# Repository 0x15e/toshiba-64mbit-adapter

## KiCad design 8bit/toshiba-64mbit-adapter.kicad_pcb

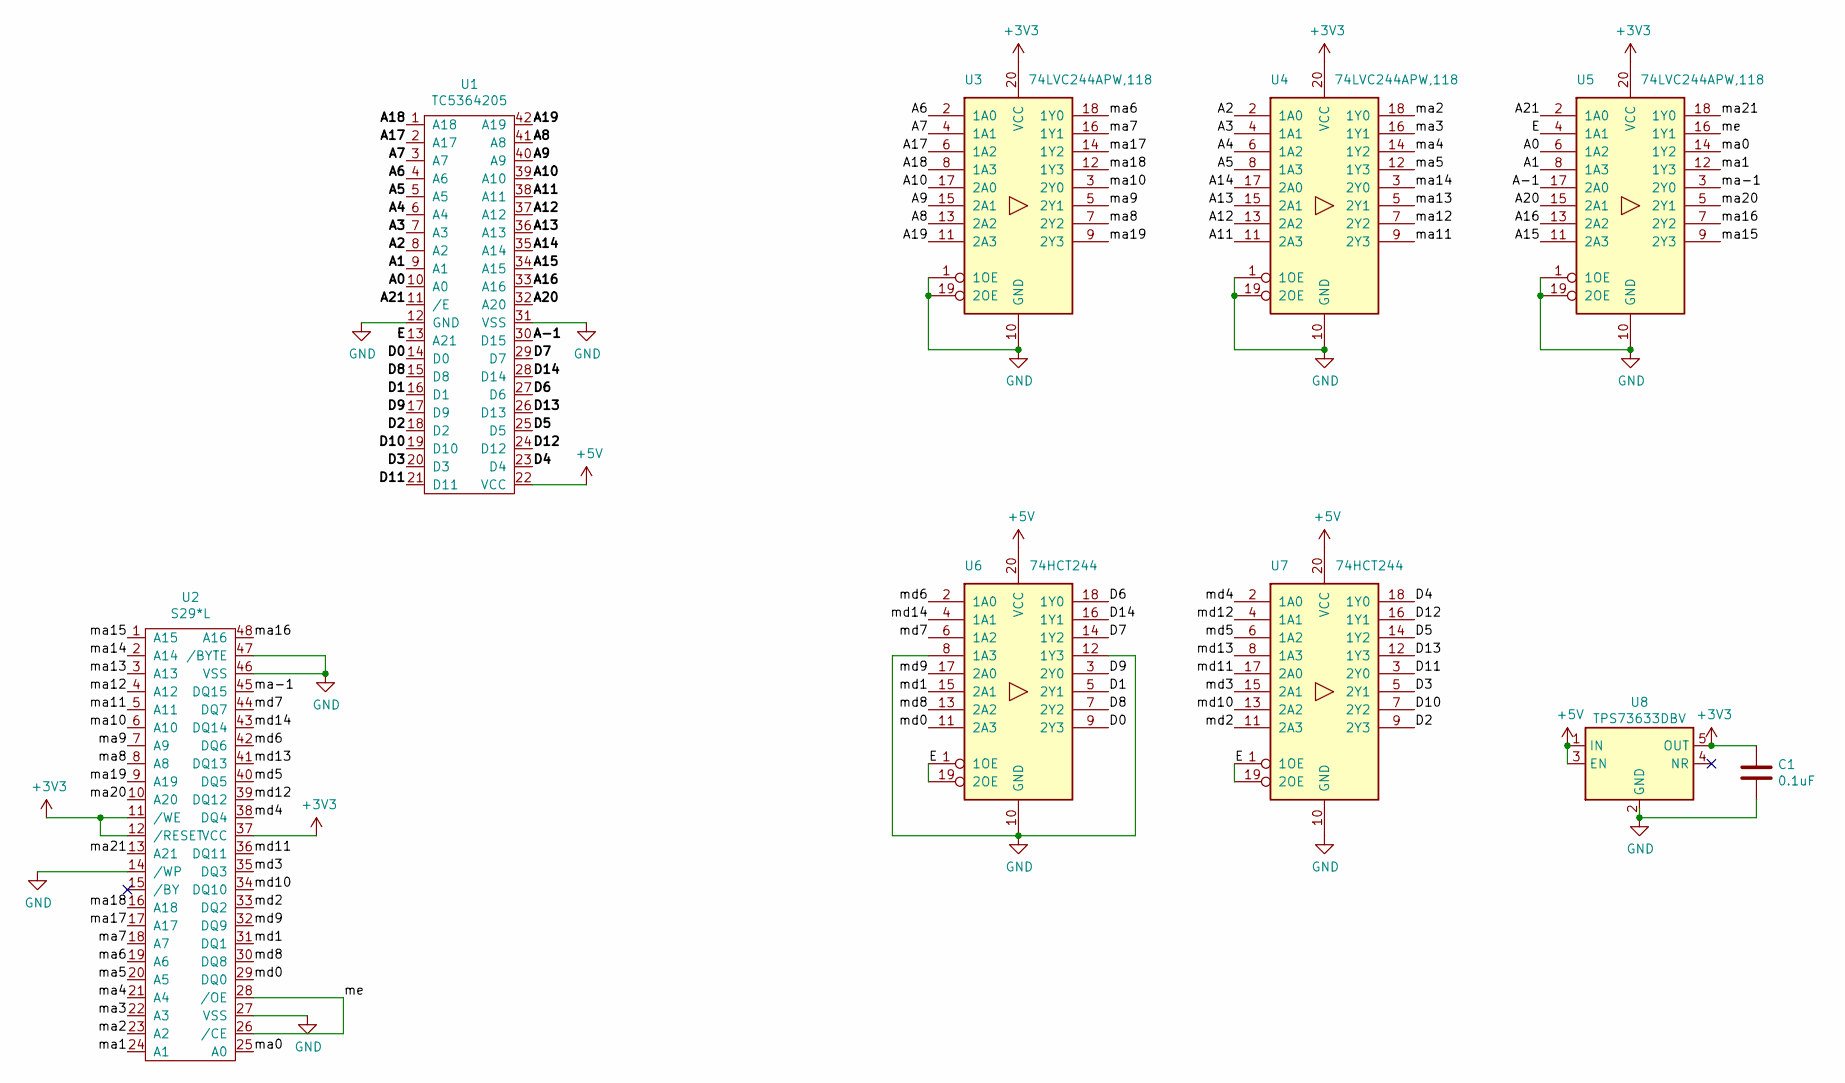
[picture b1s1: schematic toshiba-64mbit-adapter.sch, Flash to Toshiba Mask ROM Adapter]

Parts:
C1: 0.1uF; C_0805_2012Metric
U1: TC5364205; DIP-42_W15.24mm
U2: S29*L; TSOP-I-48_18.4x12mm_P0.5mm
U3, U4, U5: 74LVC244APW,118; TSSOP-20_4.4x6.5mm_P0.65mm
U6, U7: 74HCT244; TSSOP-20_4.4x6.5mm_P0.65mm
U8: TPS73633DBV; SOT-23-5

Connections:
+3V3: C1.2, U2.11 (/WE), U2.12 (/RESET), U2.37 (VCC), U3.20 (VCC), U4.20 (VCC), U5.20 (VCC), U8.5 (OUT)
+5V: U1.22 (VCC), U6.20 (VCC), U7.20 (VCC), U8.1 (IN), U8.3 (EN)
/A0: U1.10 (A0), U5.6 (1A2)
/A1: U1.9 (A1), U5.8 (1A3)
/A2: U1.8 (A2), U4.2 (1A0)
/A3: U1.7 (A3), U4.4 (1A1)
/A4: U1.6 (A4), U4.6 (1A2)
/A5: U1.5 (A5), U4.8 (1A3)
/A6: U1.4 (A6), U3.2 (1A0)
/A7: U1.3 (A7), U3.4 (1A1)
/A8: U1.41 (A8), U3.13 (2A2)
/A9: U1.40 (A9), U3.15 (2A1)
/A10: U1.39 (A10), U3.17 (2A0)
/A11: U1.38 (A11), U4.11 (2A3)
/A12: U1.37 (A12), U4.13 (2A2)
/A13: U1.36 (A13), U4.15 (2A1)
/A14: U1.35 (A14), U4.17 (2A0)
/A15: U1.34 (A15), U5.11 (2A3)
/A16: U1.33 (A16), U5.13 (2A2)
/A17: U1.2 (A17), U3.6 (1A2)
/A18: U1.1 (A18), U3.8 (1A3)
/A19: U1.42 (A19), U3.11 (2A3)
/A20: U1.32 (A20), U5.15 (2A1)
/A21: U1.11 (/E), U5.2 (1A0)
/A-1: U1.30 (D15), U5.17 (2A0)
/D0: U1.14 (D0), U6.9 (2Y3)
/D1: U1.16 (D1), U6.5 (2Y1)
/D2: U1.18 (D2), U7.9 (2Y3)
/D3: U1.20 (D3), U7.5 (2Y1)
/D4: U1.23 (D4), U7.18 (1Y0)
/D5: U1.25 (D5), U7.14 (1Y2)
/D6: U1.27 (D6), U6.18 (1Y0)
/D7: U1.29 (D7), U6.14 (1Y2)
/D8: U1.15 (D8), U6.7 (2Y2)
/D9: U1.17 (D9), U6.3 (2Y0)
/D10: U1.19 (D10), U7.7 (2Y2)
/D11: U1.21 (D11), U7.3 (2Y0)
/D12: U1.24 (D12), U7.16 (1Y1)
/D13: U1.26 (D13), U7.12 (1Y3)
/D14: U1.28 (D14), U6.16 (1Y1)
/E: U1.13 (A21), U5.4 (1A1), U6.1 (1OE), U6.19 (2OE), U7.1 (1OE), U7.19 (2OE)
/ma0: U2.25 (A0), U5.14 (1Y2)
/ma1: U2.24 (A1), U5.12 (1Y3)
/ma2: U2.23 (A2), U4.18 (1Y0)
/ma3: U2.22 (A3), U4.16 (1Y1)
/ma4: U2.21 (A4), U4.14 (1Y2)
/ma5: U2.20 (A5), U4.12 (1Y3)
/ma6: U2.19 (A6), U3.18 (1Y0)
/ma7: U2.18 (A7), U3.16 (1Y1)
/ma8: U2.8 (A8), U3.7 (2Y2)
/ma9: U2.7 (A9), U3.5 (2Y1)
/ma10: U2.6 (A10), U3.3 (2Y0)
/ma11: U2.5 (A11), U4.9 (2Y3)
/ma12: U2.4 (A12), U4.7 (2Y2)
/ma13: U2.3 (A13), U4.5 (2Y1)
/ma14: U2.2 (A14), U4.3 (2Y0)
/ma15: U2.1 (A15), U5.9 (2Y3)
/ma16: U2.48 (A16), U5.7 (2Y2)
/ma17: U2.17 (A17), U3.14 (1Y2)
/ma18: U2.16 (A18), U3.12 (1Y3)
/ma19: U2.9 (A19), U3.9 (2Y3)
/ma20: U2.10 (A20), U5.5 (2Y1)
/ma21: U2.13 (A21), U5.18 (1Y0)
/ma-1: U2.45 (DQ15), U5.3 (2Y0)
/md0: U2.29 (DQ0), U6.11 (2A3)
/md1: U2.31 (DQ1), U6.15 (2A1)
/md2: U2.33 (DQ2), U7.11 (2A3)
/md3: U2.35 (DQ3), U7.15 (2A1)
/md4: U2.38 (DQ4), U7.2 (1A0)
/md5: U2.40 (DQ5), U7.6 (1A2)
/md6: U2.42 (DQ6), U6.2 (1A0)
/md7: U2.44 (DQ7), U6.6 (1A2)
/md8: U2.30 (DQ8), U6.13 (2A2)
/md9: U2.32 (DQ9), U6.17 (2A0)
/md10: U2.34 (DQ10), U7.13 (2A2)
/md11: U2.36 (DQ11), U7.17 (2A0)
/md12: U2.39 (DQ12), U7.4 (1A1)
/md13: U2.41 (DQ13), U7.8 (1A3)
/md14: U2.43 (DQ14), U6.4 (1A1)
/me: U2.26 (/CE), U2.28 (/OE), U5.16 (1Y1)
GND: C1.1, U1.12 (GND), U1.31 (VSS), U2.14 (/WP), U2.27 (VSS), U2.46 (VSS), U2.47 (/BYTE), U3.1 (1OE), U3.10 (GND), U3.19 (2OE), U4.1 (1OE), U4.10 (GND), U4.19 (2OE), U5.1 (1OE), U5.10 (GND), U5.19 (2OE), U6.8 (1A3), U6.10 (GND), U6.12 (1Y3), U7.10 (GND), U8.2 (GND)

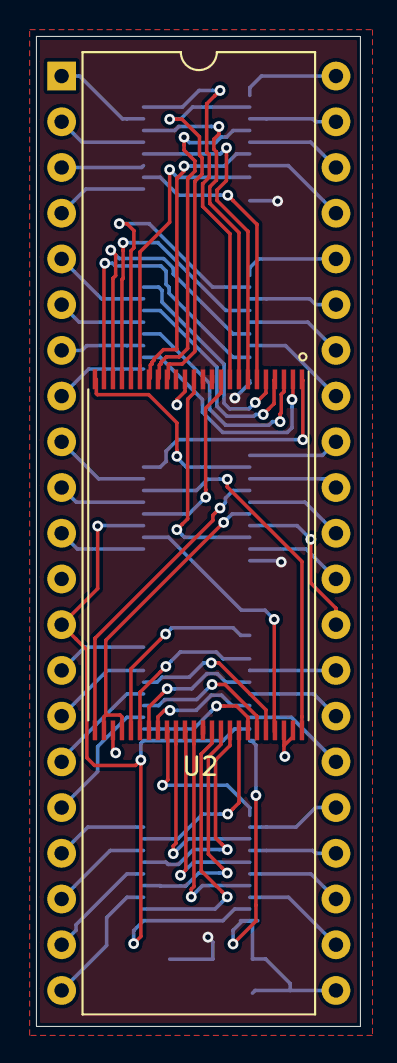
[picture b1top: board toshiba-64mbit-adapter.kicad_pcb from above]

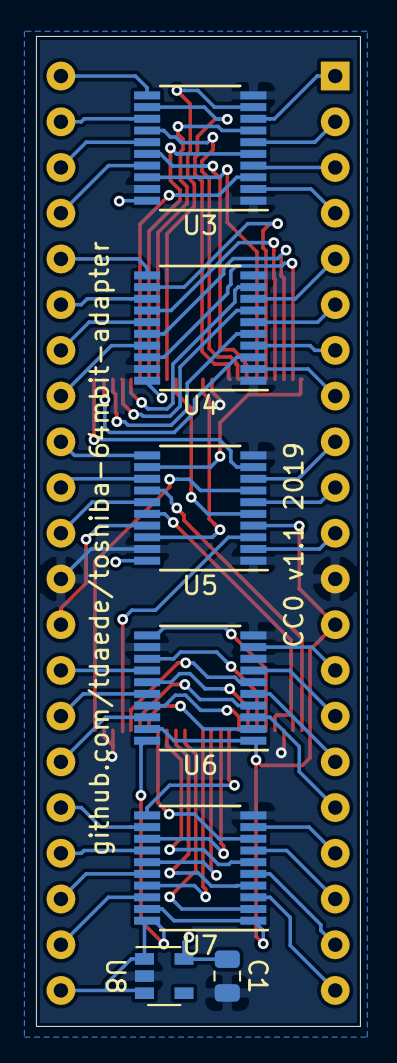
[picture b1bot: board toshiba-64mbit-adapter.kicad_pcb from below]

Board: 2 copper layers, 18.0 x 55.0 mm, 9 parts (7 on the bottom side), 81 nets.

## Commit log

2020-10-16 Backlink to CADLAB.io has been added.
2020-10-16 Updated to current KiCad stable
    - Updated project files to current KiCad stable version
    - Added gitignore to ignore backup files
2020-10-16 Labeling
    - A11 label on DIP42 is now bold to match other labels
    - Renamed U2 to indicate newer, more common parts
2020-10-16 Project setup
    - Updated schematic page settings with title, ref, license
    - Added some notes to parts and a link to a doc with a pinout for the 64Mbit Toshiba chip
    - Updated plots
2020-10-16 Reorganization
    - Moved buffers and labels around a bit to make things easier to read
    - Changed output buffers to use 5V supply
2020-11-11 Fixed part references
    - Changed some HCT parts to LVC
    - Moved some labels around a hair
2020-11-11 Added solder jumpers
    - Added solder jumpers for configuring / routing byte/word mode
    - Added footprints for solder jumpers
2021-02-01 split to separate version
    going to do this as 8bit and 16bit versions rather than a single configurable version
2021-02-01 this probably works

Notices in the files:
8bit/toshiba-64mbit-adapter.kicad_pcb:
CC0 v1.1 2019
8bit/toshiba-64mbit-adapter.sch:
License: CC0 1.0 Universal
